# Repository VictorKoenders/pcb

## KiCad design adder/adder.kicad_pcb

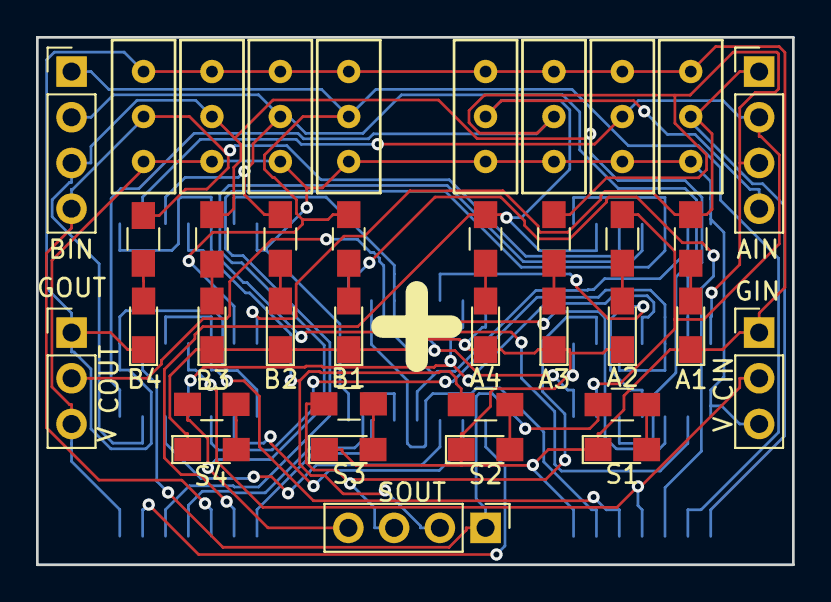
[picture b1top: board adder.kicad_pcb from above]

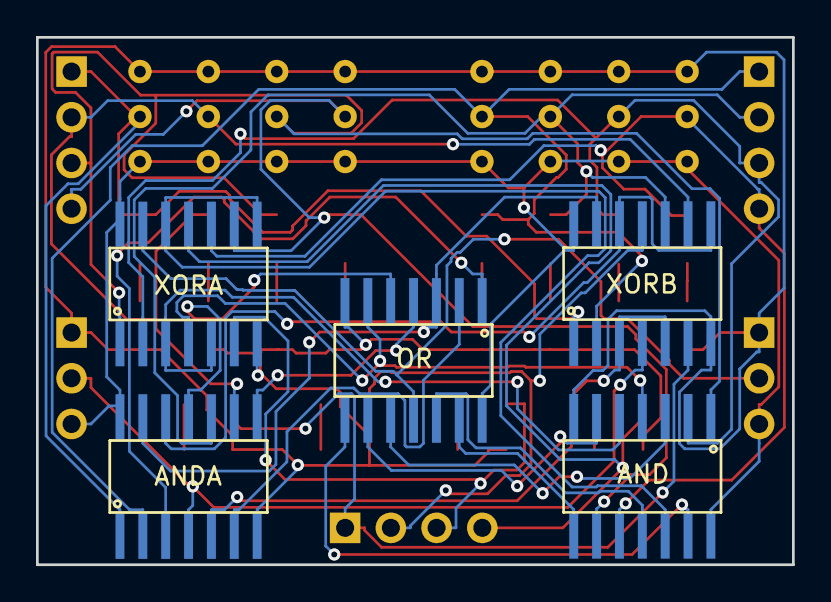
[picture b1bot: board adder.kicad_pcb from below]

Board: 2 copper layers, 42.0 x 29.3 mm, 42 parts (5 on the bottom side), 43 nets.

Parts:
A1: A1; LED_0805_HandSoldering
A2: A2; LED_0805_HandSoldering
A3: A3; LED_0805_HandSoldering
A4: A4; LED_0805_HandSoldering
AIN: AIN; Socket_Strip_Straight_1x04_Pitch2.54mm
AND: ANDB; ssop14
ANDA: AND; ssop14
B1: B1; LED_0805_HandSoldering
B2: B2; LED_0805_HandSoldering
B3: B3; LED_0805_HandSoldering
B4: B4; LED_0805_HandSoldering
BIN: BIN; Socket_Strip_Straight_1x04_Pitch2.54mm
GIN: VIN; Socket_Strip_Straight_1x03_Pitch2.54mm
GOUT: VOUT; Socket_Strip_Straight_1x03_Pitch2.54mm
IA1: A1; mini-vertical-slide-switch
IA2: A2; mini-vertical-slide-switch
IA3: A3; mini-vertical-slide-switch
IA4: A4; mini-vertical-slide-switch
IB1: B1; mini-vertical-slide-switch
IB2: B2; mini-vertical-slide-switch
IB3: B3; mini-vertical-slide-switch
IB4: B4; mini-vertical-slide-switch
OR: OR; ssop14
R1, R2, R3, R4, R5, R6, R7, R8: R; R_0805_HandSoldering
R9: S1; R_0805_HandSoldering
R10: S2; R_0805_HandSoldering
R11: S3; R_0805_HandSoldering
R12: S4; R_0805_HandSoldering
S1: S1; LED_0805_HandSoldering
S2: S2; LED_0805_HandSoldering
S3: S3; LED_0805_HandSoldering
S4: S4; LED_0805_HandSoldering
SOUT: SOUT; Socket_Strip_Straight_1x04_Pitch2.54mm
XORA: XOR; ssop14
XORB: XOR; ssop14

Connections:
+5V: AND.14, ANDA.14, GIN.3, GOUT.3, IA1.3, IA2.3, IA3.3, IA4.3, IB1.3, IB2.3, IB3.3, IB4.3, OR.14, XORA.14, XORB.14
/A1: AIN.1, ANDA.1, IA1.1, R1.2, XORB.1
/A2: AIN.2, ANDA.9, IA2.1, R3.2, XORB.9
/A3: AIN.3, AND.1, IA3.1, R5.2, XORA.1
/A4: AIN.4, AND.9, IA4.1, R7.2, XORA.9
/AAB1: ANDA.3, OR.1
/AAB2: ANDA.8, OR.4
/AAB3: AND.3, OR.10
/AAB4: AND.8, OR.13
/B1: ANDA.2, BIN.1, IB1.1, R2.2, XORB.2
/B2: ANDA.10, BIN.2, IB2.1, R4.2, XORB.10
/B3: AND.2, BIN.3, IB3.1, R6.2, XORA.2
/B4: AND.10, BIN.4, IB4.1, R8.2, XORA.10
/C1: ANDA.13, OR.3, XORB.13
/C2: AND.4, OR.6, XORA.4
/C3: AND.13, OR.8
/CIN: ANDA.4, GIN.2, XORB.4
/COUT: GOUT.2, OR.11, XORA.13
/S1: R9.2, SOUT.1, XORB.6
/S2: R10.2, SOUT.2, XORB.11
/S3: R11.2, SOUT.3, XORA.6
/S4: R12.2, SOUT.4, XORA.11
/XAAB1: ANDA.6, OR.2
/XAAB2: ANDA.11, OR.5
/XAAB3: AND.6, OR.9
/XAAB4: AND.11, OR.12
/XAB1: ANDA.5, XORB.3, XORB.5
/XAB2: ANDA.12, XORB.8, XORB.12
/XAB3: AND.5, XORA.3, XORA.5
/XAB4: AND.12, XORA.8, XORA.12
GND: A1.1, A2.1, A3.1, A4.1, AND.7, ANDA.7, B1.1, B2.1, B3.1, B4.1, GIN.1, GOUT.1, IA1.2, IA2.2, IA3.2, IA4.2, IB1.2, IB2.2, IB3.2, IB4.2, OR.7, S1.1, S2.1, S3.1, S4.1, XORA.7, XORB.7
unnamed: A1.2, R1.1
unnamed: B1.2, R2.1
unnamed: A2.2, R3.1
unnamed: B2.2, R4.1
unnamed: A3.2, R5.1
unnamed: B3.2, R6.1
unnamed: A4.2, R7.1
unnamed: B4.2, R8.1
unnamed: R9.1, S1.2
unnamed: R10.1, S2.2
unnamed: R11.1, S3.2
unnamed: R12.1, S4.2

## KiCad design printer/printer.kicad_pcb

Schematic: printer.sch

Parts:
A1, A2, A3, A4: Pololu_Breakout_A4988; Pololu_Breakout-16_15.2x20.3mm
BED1: Screw_Terminal_01x04; TerminalBlock_bornier-4_P5.08mm
IRFZ44N_1, IRFZ44N_2, IRFZ44N_3, IRFZ44N_4: IRF3205; TO-220-3_Vertical
MOTOR_X1: Stepper_Motor_bipolar; PinHeader_1x04_P2.54mm_Vertical
MOTOR_Y1: Stepper_Motor_bipolar; PinHeader_1x04_P2.54mm_Vertical
MOTOR_Z1, MOTOR_Z2: Stepper_Motor_bipolar; PinHeader_1x04_P2.54mm_Vertical
NOZZLE1: Screw_Terminal_01x04; TerminalBlock_bornier-4_P5.08mm
NOZZLE_FAN1: Screw_Terminal_01x02; TerminalBlock_bornier-2_P5.08mm
POWER_1: Screw_Terminal_01x04; TerminalBlock_bornier-4_P5.08mm
PRINT_FAN1: Screw_Terminal_01x02; TerminalBlock_bornier-2_P5.08mm
R1, R2, R3, R4: 10K; R_0805_2012Metric_Pad1.15x1.40mm_HandSolder
RESET1: SW_Push; PinHeader_1x02_P2.54mm_Vertical
SD_CARD_1: Conn_01x06; PinHeader_1x06_P2.54mm_Vertical
SERIAL1: Conn_01x06; PinHeader_1x06_P2.54mm_Vertical
STM32F103: STM32F103; stm32f103
X_END1: SW_Push; PinHeader_1x02_P2.54mm_Vertical
Y_END1: SW_Push; PinHeader_1x02_P2.54mm_Vertical
Z_END1, Z_END2: SW_Push; PinHeader_1x02_P2.54mm_Vertical

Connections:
+5V: NOZZLE_FAN1.2, POWER_1.1, PRINT_FAN1.2, SD_CARD_1.5, SERIAL1.1, STM32F103.5V
+12V: A1.8, A2.8, A3.8, A4.8, BED1.3, NOZZLE1.3, POWER_1.4
/3V3: A1.2, A1.10, A1.13, A1.14, A2.2, A2.10, A2.13, A2.14, A3.2, A3.10, A3.13, A3.14, A4.2, A4.10, A4.13, A4.14, BED1.2, NOZZLE1.2, R1.1, R2.1, R3.1, R4.1, SERIAL1.6, STM32F103.3V3, STM32F103.VBAT
/rx: SERIAL1.3, STM32F103.PA10
/spi_miso: SD_CARD_1.4, STM32F103.PA6
/spi_mosi: SD_CARD_1.3, STM32F103.PA7
/spi_sck: SD_CARD_1.2, STM32F103.PA5
/temp_bed: BED1.1, STM32F103.PB0
/temp_nozzle: NOZZLE1.1, STM32F103.PB1
/toggle_bed: IRFZ44N_1.1 (G), STM32F103.PB5
/toggle_nozzle: IRFZ44N_2.1 (G), STM32F103.PB4
/toggle_nozzle_fan: IRFZ44N_3.1 (G), STM32F103.PB6
/toggle_print_fan: IRFZ44N_4.1 (G), STM32F103.PB7
/tx: SERIAL1.4, STM32F103.PA9
/x_dir: A1.16, STM32F103.PB9
/x_end: R1.2, STM32F103.PA0, X_END1.1
/x_step: A1.15, STM32F103.PB8
/y_dir: A4.16, STM32F103.PB11
/y_end: R2.2, STM32F103.PA1, Y_END1.1
/y_step: A4.15, STM32F103.PB10
/z1_dir: A2.16, STM32F103.PB13
/z1_step: A2.15, STM32F103.PB12
/z2_dir: A3.16, STM32F103.PB15
/z2_step: A3.15, STM32F103.PB14
/z_end_1: R3.2, STM32F103.PA2, Z_END1.1
/z_end_2: R4.2, STM32F103.PA3, Z_END2.1
GND: A1.1, A1.7, A1.9, A1.11, A1.12, A2.1, A2.7, A2.9, A2.11, A2.12, A3.1, A3.7, A3.9, A3.11, A3.12, A4.1, A4.7, A4.9, A4.11, A4.12, IRFZ44N_1.3 (S), IRFZ44N_2.3 (S), IRFZ44N_3.3 (S), IRFZ44N_4.3 (S), POWER_1.2, POWER_1.3, RESET1.2, SD_CARD_1.6, SERIAL1.2, STM32F103.G, X_END1.2, Y_END1.2, Z_END1.2, Z_END2.2
unnamed: A1.3, MOTOR_X1.2
unnamed: A1.4, MOTOR_X1.1
unnamed: A1.5, MOTOR_X1.3
unnamed: A1.6, MOTOR_X1.4
unnamed: A2.3, MOTOR_Z1.2
unnamed: A2.4, MOTOR_Z1.1
unnamed: A2.5, MOTOR_Z1.3
unnamed: A2.6, MOTOR_Z1.4
unnamed: A3.3, MOTOR_Z2.2
unnamed: A3.4, MOTOR_Z2.1
unnamed: A3.5, MOTOR_Z2.3
unnamed: A3.6, MOTOR_Z2.4
unnamed: A4.3, MOTOR_Y1.2
unnamed: A4.4, MOTOR_Y1.1
unnamed: A4.5, MOTOR_Y1.3
unnamed: A4.6, MOTOR_Y1.4
unnamed: BED1.4, IRFZ44N_1.2 (D)
unnamed: IRFZ44N_2.2 (D), NOZZLE1.4
unnamed: IRFZ44N_3.2 (D), NOZZLE_FAN1.1
unnamed: IRFZ44N_4.2 (D), PRINT_FAN1.1
unnamed: RESET1.1, STM32F103.NRST

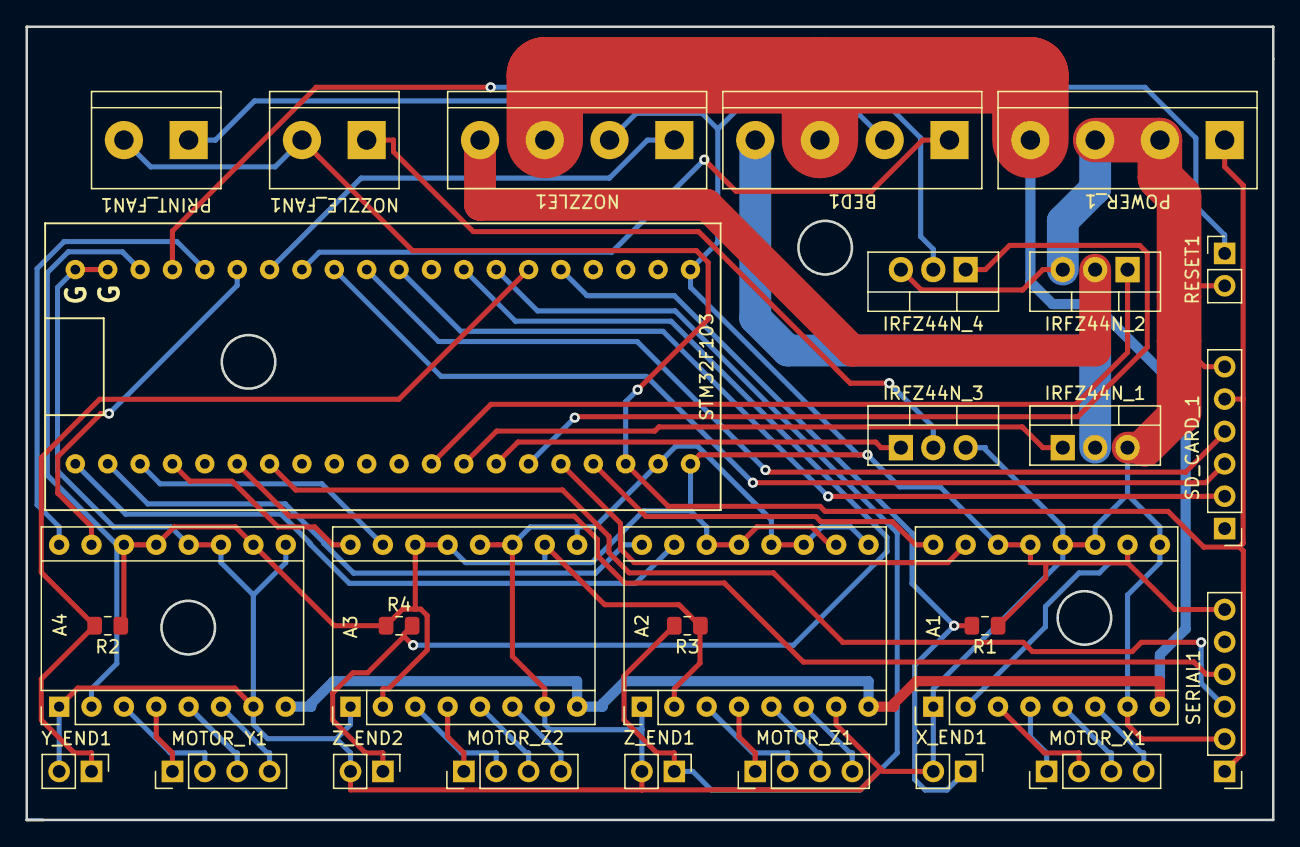
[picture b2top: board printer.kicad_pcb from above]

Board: 2 copper layers, 97.8 x 62.2 mm, 29 parts (0 on the bottom side), 48 nets.

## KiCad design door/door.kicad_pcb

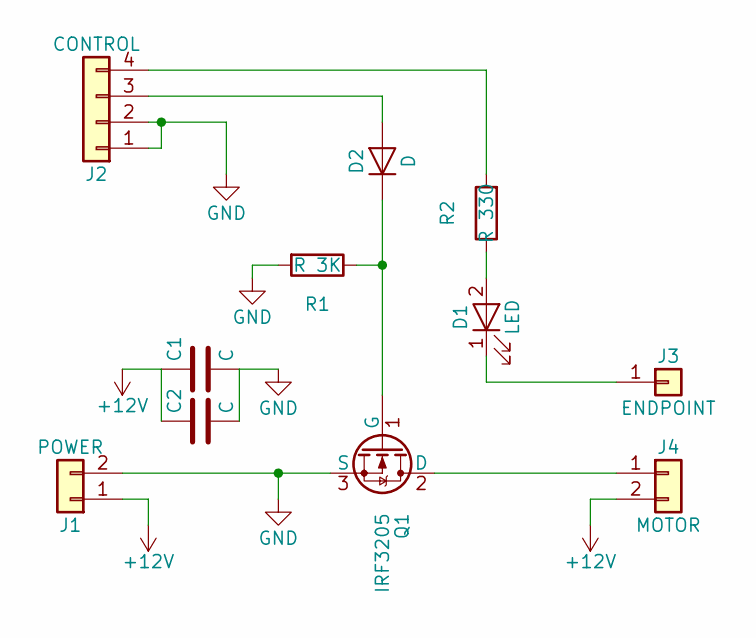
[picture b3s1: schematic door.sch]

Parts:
C1, C2: C; CP_Radial_D7.5mm_P2.50mm
D1: LED; LED_0805_HandSoldering
D2: D; R_0805_HandSoldering
J1: POWER; screw-terminal-01x02
J2: CONTROL; Pin_Header_Straight_1x04_Pitch2.54mm
J3: ENDPOINT; Pin_Header_Straight_1x01_Pitch2.54mm
J4: MOTOR; screw-terminal-01x02
Q1: IRF3205; TO-220-3_Vertical
R1: R 3K; R_0805_HandSoldering
R2: R 330; R_0805_HandSoldering

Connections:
+12V: C1.1, C2.1, J1.1, J4.2
GND: C1.2, C2.2, J1.2, J2.1, J2.2, Q1.3 (S), R1.2
unnamed: D1.1 (K), J3.1
unnamed: D1.2 (A), R2.1
unnamed: D2.1 (K), Q1.1 (G), R1.1
unnamed: D2.2 (A), J2.3
unnamed: J2.4, R2.2
unnamed: J4.1, Q1.2 (D)

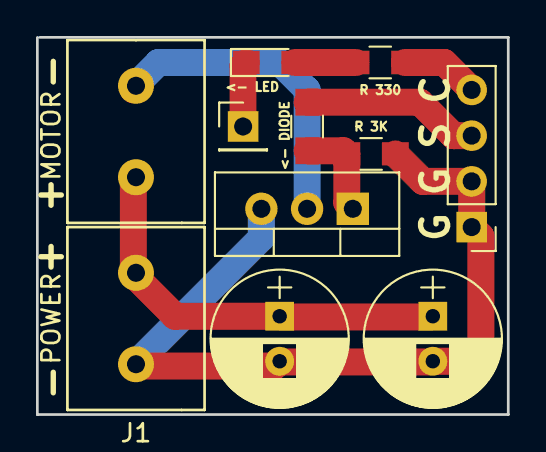
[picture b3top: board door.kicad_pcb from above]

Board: 2 copper layers, 26.2 x 21.0 mm, 11 parts (0 on the bottom side), 8 nets.

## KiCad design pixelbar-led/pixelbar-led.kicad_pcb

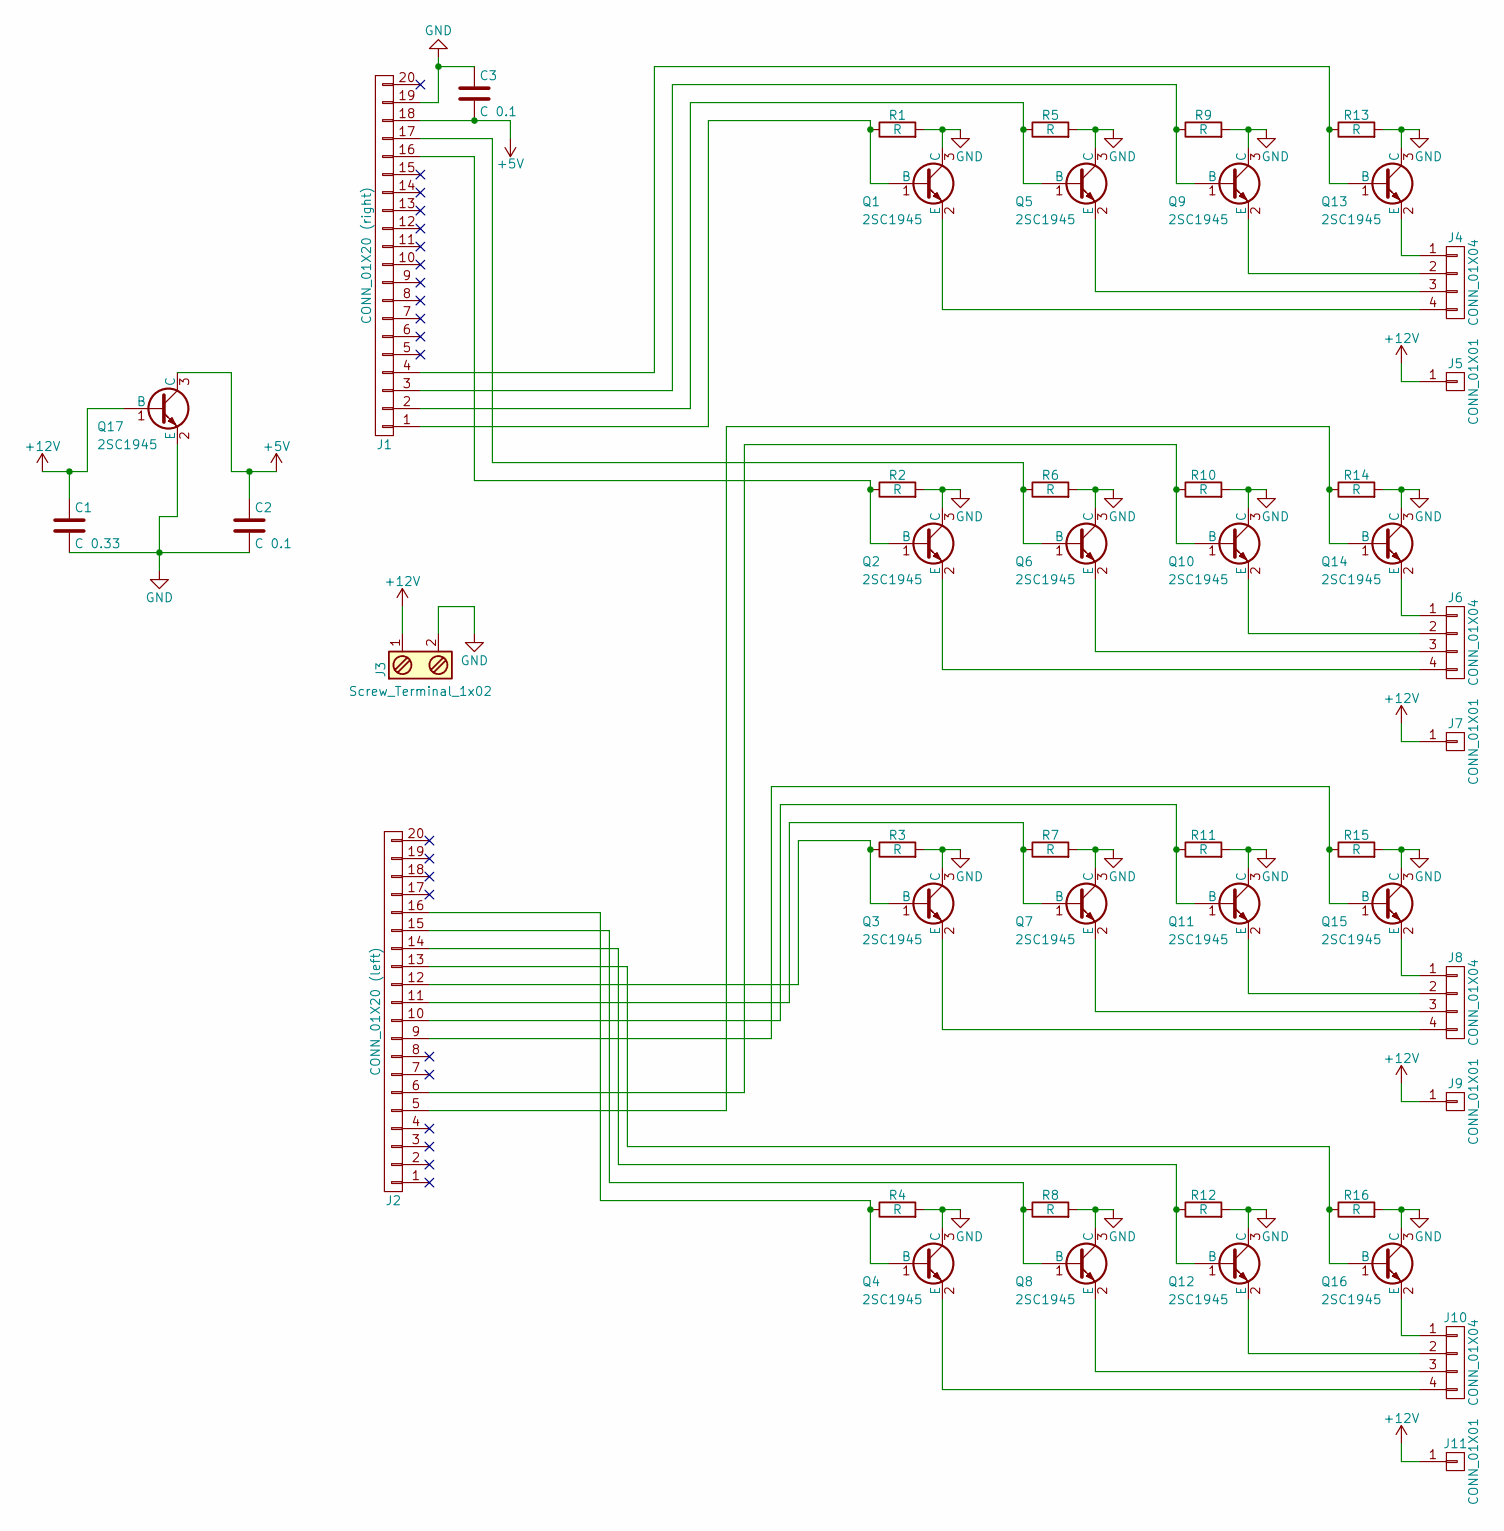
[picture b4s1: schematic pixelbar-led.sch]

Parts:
C1: C 0.33; C_0805
C2, C3: C 0.1; C_0805
J1: CONN_01X20 (right); Socket_Strip_Straight_1x20_Pitch2.00mm
J2: CONN_01X20 (left); Socket_Strip_Straight_1x20_Pitch2.00mm
J3: Screw_Terminal_1x02; TerminalBlock_Pheonix_MKDS1.5-2pol
J4, J6, J8, J10: CONN_01X04; Socket_Strip_Straight_1x04_Pitch2.54mm
J5, J7, J9, J11: CONN_01X01; Socket_Strip_Straight_1x01_Pitch2.54mm
Q1, Q2, Q3, Q4, Q5, Q6, Q7, Q8, Q9, Q10, Q11, Q12, Q13, Q14, Q15, Q16, Q17: 2SC1945; TO-220_Horizontal
R1, R2, R3, R4, R5, R6, R7, R8, R9, R10, R11, R12, R13, R14, R15, R16: R; R_0805

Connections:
+5V: C2.1, C3.2, J1.18, Q17.3 (C)
+12V: C1.1, J3.1, J5.1, J7.1, J9.1, J11.1, Q17.1 (B)
GND: C1.2, C2.2, C3.1, J1.19, J3.2, Q1.3 (C), Q2.3 (C), Q3.3 (C), Q4.3 (C), Q5.3 (C), Q6.3 (C), Q7.3 (C), Q8.3 (C), Q9.3 (C), Q10.3 (C), Q11.3 (C), Q12.3 (C), Q13.3 (C), Q14.3 (C), Q15.3 (C), Q16.3 (C), Q17.2 (E), R1.2, R2.2, R3.2, R4.2, R5.2, R6.2, R7.2, R8.2, R9.2, R10.2, R11.2, R12.2, R13.2, R14.2, R15.2, R16.2
unnamed: J1.1, Q1.1 (B), R1.1
unnamed: J1.2, Q5.1 (B), R5.1
unnamed: J1.3, Q9.1 (B), R9.1
unnamed: J1.4, Q13.1 (B), R13.1
unnamed: J1.16, Q2.1 (B), R2.1
unnamed: J1.17, Q6.1 (B), R6.1
unnamed: J2.5, Q14.1 (B), R14.1
unnamed: J2.6, Q10.1 (B), R10.1
unnamed: J2.9, Q15.1 (B), R15.1
unnamed: J2.10, Q11.1 (B), R11.1
unnamed: J2.11, Q7.1 (B), R7.1
unnamed: J2.12, Q3.1 (B), R3.1
unnamed: J2.13, Q16.1 (B), R16.1
unnamed: J2.14, Q12.1 (B), R12.1
unnamed: J2.15, Q8.1 (B), R8.1
unnamed: J2.16, Q4.1 (B), R4.1
unnamed: J4.1, Q13.2 (E)
unnamed: J4.2, Q9.2 (E)
unnamed: J4.3, Q5.2 (E)
unnamed: J4.4, Q1.2 (E)
unnamed: J6.1, Q14.2 (E)
unnamed: J6.2, Q10.2 (E)
unnamed: J6.3, Q6.2 (E)
unnamed: J6.4, Q2.2 (E)
unnamed: J8.1, Q15.2 (E)
unnamed: J8.2, Q11.2 (E)
unnamed: J8.3, Q7.2 (E)
unnamed: J8.4, Q3.2 (E)
unnamed: J10.1, Q16.2 (E)
unnamed: J10.2, Q12.2 (E)
unnamed: J10.3, Q8.2 (E)
unnamed: J10.4, Q4.2 (E)

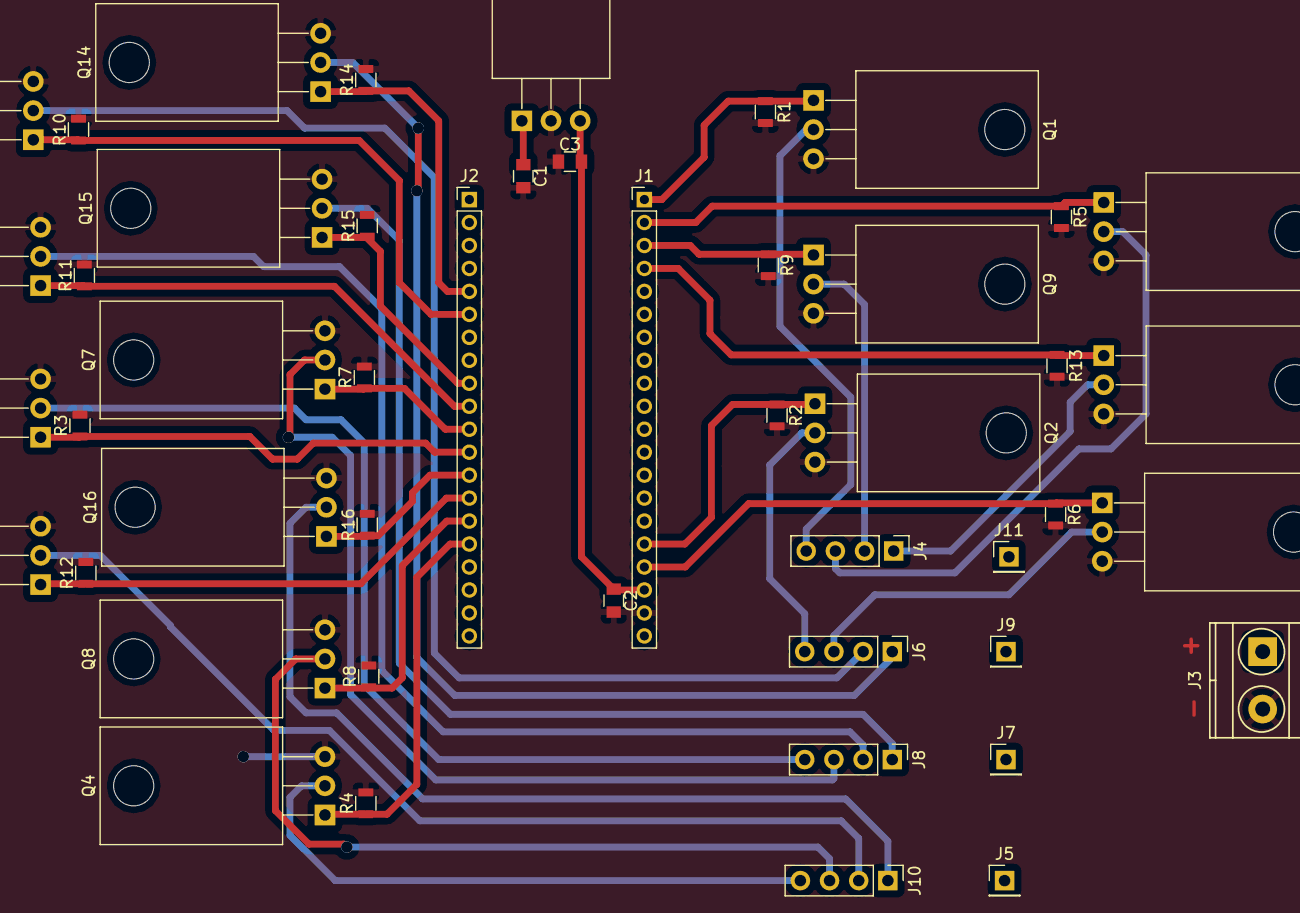
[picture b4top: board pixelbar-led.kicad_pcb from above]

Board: 2 copper layers, 47 parts (0 on the bottom side), 35 nets.

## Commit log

2017-12-09 Added door controller
2017-12-10 Added pixelbar-led and walking_bot
2017-12-10 Made the door pcb half the size
2017-12-10 Added diode to the door signal
2017-12-10 Fixed text layers
2018-01-03 Updated screw terminal footprint
2018-01-03 Updated screw terminal footprint and moved components around
2018-01-06 Fixed text-based issues and updated screw terminal footprint
2018-01-06 Started dino project
2018-01-15 Added 30 LEDs and controllers
2018-02-20 Added vertical slider and started on adder project
2018-02-20 First (incomplete) version of a 4-bit adder
2018-02-21 Finished diagram and started on pcb layout hell
2018-02-21 Updated traces to match OshPark's
2018-02-21 Did some more work on the PCB design hell
2018-05-16 Finished v2 of adder
2018-05-16 Started on adder v3
2018-09-08 Added stm32 to libraries
2018-09-08 First version of my printer PCB
2018-09-08 Minor tweaks
2018-09-08 Updated adder
